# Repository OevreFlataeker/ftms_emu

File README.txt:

Used SDK 17.0.2
DevKit: NRF52DK

D:\nRF5_SDK_17.0.2_d674dde\examples\ble_central_and_peripheral\experimental\ble_app_cps_relay

Most of the headers comments have been explicitly removed in order to avoid confusion which parts are
genuine Nordic and which not

All 3rd party contrib stuff has been removed (FIT files, PCAP, BLE Sniffer, ...)

All Spec PDFs have been removed

---
---
---

Merged back to master

Do not forget to add the services 0x1814 (RCS) or 0x1816 (CSC) to the ADV Data! 
Otherwise it won't be found!

Macros
#define 	PM_CONN_SEC_ERROR_PIN_OR_KEY_MISSING   (PM_CONN_SEC_ERROR_BASE + 0x06)
 	Encryption failed because the peripheral has lost the LTK for this bond. See also BLE_HCI_STATUS_CODE_PIN_OR_KEY_MISSING and Table 3.7 ("Pairing Failed Reason Codes") in the Bluetooth Core Specification 4.2, section 3.H.3.5.5 (Bluetooth Core Specification).
	
#define 	PM_CONN_SEC_ERROR_DISCONNECT   (PM_CONN_SEC_ERROR_BASE + 0x100)
 	Pairing or encryption did not finish before the link disconnected for an unrelated reason.

When bonding fails, press Button 2 + RESET to delete bonding data.

Specifications:
https://github.com/oesmith/gatt-xml/blob/master/org.bluetooth.characteristic.csc_measurement.xml
https://www.bluetooth.org/docman/handlers/downloaddoc.ashx?doc_id=261450

At the moment this whole project needs to be placed into

$SDKROOT\examples\ble_central_and_peripheral\experimental\ble_app_cps_relay
because of the relative include directory setup

e.g. D:\nRF5_SDK_17.0.2_d674dde\examples\ble_central_and_peripheral\experimental\ble_app_cps_relay

Bike physics: https://www.physik.uni-wuerzburg.de/fileadmin/11010700/_imported/fileadmin/11010700/Didaktik/Zulassungsarbeiten/HA_1622196_Bielmeier_Carsten.pdf?
Section 5.2.3 - Free rolling

Formular free roll: v(t)=45*exp(-0.04*t)

Power measurement series:

Level 1:
76,58
77,59
79,61
80,62

Level 2:
74,67
75,69
77,71
78,72
79,73
80,75

Level 3:
75,80
76,81
79,84
80,86

Level 4:
76,94
77,96
78,98
79,100
80,102

Level 5:
77,110
78,112
80,116
81,117

Level 6:
75,120
76,120
78,124
78,124
79,126
80,128

Level 7:
75,129
76,131
77,133
78,135
81,141

Level 8:
75,141
77,145
78,148
80,153

Level 9:
76,157
77,159
78,162
80,168
80,168
80,169
84,175

Level 10:
80,178

Level 11:

74,173
75,175
76,178
77,181
78,184
79,187
79,187
80,190
80,190
82,136
Watt = 190-(rpm-80)*3

Level 12:
76,188
77,191
78,194
80,200
84,211
Watt = 200-(rpm-80)*3

Level 13:
76,198
77,201
78,204
79,207
80,210
Watt = 210-(rpm-80)*3

Level 14:
77,210
78,213
79,216
79,217
80,220
84,230
85,233
Watt = 220-(rpm-80)*3

Level 15:
72,204
73,207
74,210
75.215
80,230
82,232
82,235
85,238
Watt = 230-(rpm-80)*3

Level 16:
71,211
72,215
76,229
77,232
78,236
78,236
79,239
80,243
Watt = 236-(rpm-78)*4

Level 17:
72,229
74,233
75,237
76,240
76,240
77,244
78,247
Watt = 240+(rpm-76)*4

Level 18:
72,236
73,240
75,248
75,248
76,251
77,255
78,259
Watt = 248+(rpm-75)*4

Level 19:
74,253
75,257
76,261
77,265
Watt = 258+(rpm-75)*4

Level 20:
70,244
71,248
73,256
74,260
Watt = 260+(rpm-74)*4

Polar:
https://www.polar.com/sites/default/files/static/science/white-papers/polar-smart-calories-white-paper.pdf

Energy Expediture:
https://www.researchgate.net/publication/7777759_Prediction_of_energy_expenditure_from_heart_rate_monitoring_during_submaximal_exercise
EE = gender x (-55.0969 + 0.6309 x heart rate + 0.1988 x weight + 0.2017 x age)
+ (1 - gender) x (-20.4022 + 0.4472 x heartrate - 0.1263 x weight + 0.074 x age)
where gender = 1 for males and 0 for females. 

or:
https://www.sciencedirect.com/science/article/pii/S2095254612000464
for men, REE = 66.5 + 13.75 × weight (kg) + 5.003 × height (cm) − 6.775 × age; for women, REE = 655.1 + 9.563 × weight (kg) + 1.850 × height (cm) − 4.676 × age.

Calculator cadence:
https://www.omnicalculator.com/sports/bike-cadence-and-speed-calculator

https://www.bikecalc.com/speed_at_cadence

External buttons connection:

Candidates P0.11, P0.12, P0.22 + GND 

FTMS:
https://stackoverflow.com/questions/59653425/zwift-add-resistance-with-ftms-control-point

When an app like Zwift write to the CP it's an OP Code optionally followed by parameters, you should reply with the OP Code 0x80 (Response Code) followed by the OP Code that the reply is for, optionally followed by parameters.

In the case of OP Code 0x00 (Request Control) you should therefore reply with: 0x80, 0x00, 0x01. The last 0x01 is the result code for "Success".

In the case of OP Code 0x07 (Start/Resume), you should reply with: 0x80, 0x07, 0x01. Assuming you consider the request successful, the other possible responses are detailed in Table 4.24 of the FTMS Specification PDF.

On command you should look into is OP Code 0x11. When running Zwift in "non-workout mode", so just the normal mode, Zwift will use OP Code 0x11 followed by a set of simulation parameters: Wind Speed, Grade, Rolling resistance coeff and Wind resistance coeff. See the "4.16.2.18 Set Indoor Bike Simulation Parameters Procedure" of the PDF for details on the format of those parameters.

https://github.com/erikboto/ftms-example
https://forums.garmin.com/developer/connect-iq/f/app-ideas/206704/developing-a-ciq-ble-client-for-treadmill-and-fitness-equipment
Fitness Machine Service UUID: 0x1826
Fitness Machine Feature Characteristic 0x2acc 

Treadmill Data Characteristic 0x2acd
2902 Enable Notify Descriptor 0x2902
This is required so client gets more than one data point.
Supported Speed Range Characteristic 0x2ad4
Supported Incline Range Characteristic 0x2ad5
Keep Alive UUID

https://github.com/chadj/gpedal
https://devzone.nordicsemi.com/f/nordic-q-a/56370/bluetooth-ble-52832-try-to-implement-ftms-control-point-with-zwift
https://devzone.nordicsemi.com/f/nordic-q-a/56157/ble--nrfconnect-ftms-profile-indoor-bike-data-characteristic
https://devzone.nordicsemi.com/f/nordic-q-a/31046/how-to-support-ble-ftmp-profile
https://github.com/zacharyedwardbull/pycycling
The SufferFest, TrainerRoad, and Kinomap are the only two that I know of. 

ANT FE-C:
https://devzone.nordicsemi.com/f/nordic-q-a/44110/fe-c-support
https://github.com/vincent290587/ant_profiles

https://github.com/microsoft/BluetoothLEExplorer

https://stackoverflow.com/questions/64002583/decode-bluetooth-data-from-the-indoor-bike-data-characteristic/64004591#64004591

Tacx I/O FE-C
https://github.com/abellono/tacx-ios-bluetooth-example

https://github.com/jedla22/BleTrainerControl/blob/97f8fcefe4eb8563b768818658a1b480e10bd1b2/BleTrainerControl/BTLETrainerManager.m#L824
https://github.com/weinzmi/daumUSB2BLE/blob/master/BLE/fitness-control-point-characteristic.js#L128

Firmware download URL
https://device.tacxtraining.com/firmware/update.json

https://github.com/DigitalSecurity/nrf5x-tools

https://device.tacxtraining.com/firmware/neo_sb_pack_v0.0.40.zip

//Tacx FE-C service and characteristics
#define TACX_FEC_PRIMARY_SERVICE @"6E40FEC1-B5A3-F393-E0A9-E50E24DCCA9E"
//Pour détecter le Vortex
#define TACX_VORTEX_PRIMARY_SERVICE @"669AA305-0C08-969E-E211-86AD5062675F"

#define TACX_FEC_READ_CHARACTERISTIC @"6E40FEC2-B5A3-F393-E0A9-E50E24DCCA9E"
#define TACX_FEC_WRITE_CHARACTERISTIC @"6E40FEC3-B5A3-F393-E0A9-E50E24DCCA9E"

test: a4 09 4e 05 31 ff ff ff ff ff 90 01 b9 - set watt to 100W (= 400 * 0.25W)
test: a4 09 4e 05 31 ff ff ff ff ff 80 04 ac - set watt to 300w ( = 1200 * 0.25W)
test: a4 09 4e 05 33 ff ff ff ff 32 00 32 77 -  set incline to 50, roll resistance 0x32
test: a4 09 4e 05 33 ff ff ff ff 96 00 32 d3 -  set incline to 150
      a4 03 4e 05 46 47 ed - request data page 76 (last command)
	  a4 03 4e 05 46 10 ba - request type. 2nd byte in response = type of equipment (25 / 0x19 = Indoor bike)
Sync: 0xa4
Length: 0x09  (Data+Chk)
Type: 0x4e
Channel: 0x05
Data: 0x10 0x19 0x04 0x00 0x00 0x00 0xff 0x24
Chk(XOR of EVERYTHING): 0x30

Basline resistance values:
https://zwiftinsider.com/wahoo-kickr-tests-connecting-via-legacy-ant-ant-fe-c-and-bluetooth-ftms/
https://forums.zwift.com/t/baseline-resistance-too-low-in-sim-mode/497294

Trainer force curves:
http://www.powercurvesensor.com/cycling-trainer-power-curves/

https://devzone.nordicsemi.com/f/nordic-q-a/23316/nrf_error_no_mem

https://bicycles.stackexchange.com/questions/49732/does-changing-gear-relation-produce-different-speed-at-same-applied-power

Power via battery:

USB and coin cell at the same time is OK as long as protection diodes are not shorted: https://devzone.nordicsemi.com/f/nordic-q-a/44780/can-we-supply-power-from-both-usb-and-coin-cell-battery

Infos about battery:
https://www.dmcinfo.com/Portals/0/Blog%20Files/High%20pulse%20drain%20impact%20on%20CR2032%20coin%20cell%20battery%20capacity.pdf

Info about nrf51 sampling battery voltage via saadc
https://github.com/NordicPlayground/nrf51-ADC-examples/blob/master/ble_app_hrs_adc_battery_measurement/main.c

There should be an Input PIN 
https://github.com/NordicPlayground/nRF52-ADC-examples
https://github.com/NordicPlayground/nRF52-ADC-examples/blob/master/ble_app_uart__saadc_timer_driven__scan_mode/main.c

nrf_saadc_input_t NRF_SAADC_INPUT_VDD
nrf_saadc_reference_t NRF_SAADC_REFERENCE_VDD4 
battery_level_in_percent in https://infocenter.nordicsemi.com/topic/sdk_nrf5_v17.0.2/group__app__util.html

Important finding: The DK52 has protection diodes on all 3 powering options which lead to a drop of 0.5V on every option. Instead of 3.3V via USB its only 2.8V, Instead of 3V for the coin cell, its only 2.5V... My calculations for the triggering of the home trainer are based on a voltage of 3V (resistor, current, ..). The voltage of 2.5V is too low to trigger the shift! Actually, even at 2.8V it's a wonder it actually works...

USB A Host Interface: https://learn.sparkfun.com/tutorials/usb-type-a-female-breakout-hookup-guide/all

Central micro on hometrainer is presumably a Reneasas R8C/24, https://www.digchip.com/datasheets/parts/datasheet/192/R5F21258SNFP-pdf.php
Latest datasheet https://www.renesas.com/br/en/document/dst/r8c24-r8c25-group-datasheet?language=en&r=1053566

Hometrainer, 4 pin "Sensor" Cable:
(Note: Colors are relativ to my Y-Splitter cable!)
Yellow: GND
Red: Power settings, ranging from 1.375V (Resistance 1) to 3.9V (Resistance 32) [1: 1.375V, 10: 2.4V, 20: 3.18V, 30: 3.8V, 32: 3.9V]
White: 5V, Cadence signal, on every full revolution, signal goes Low for n ms (100?)
Black: 12V, can be used to get some voltage

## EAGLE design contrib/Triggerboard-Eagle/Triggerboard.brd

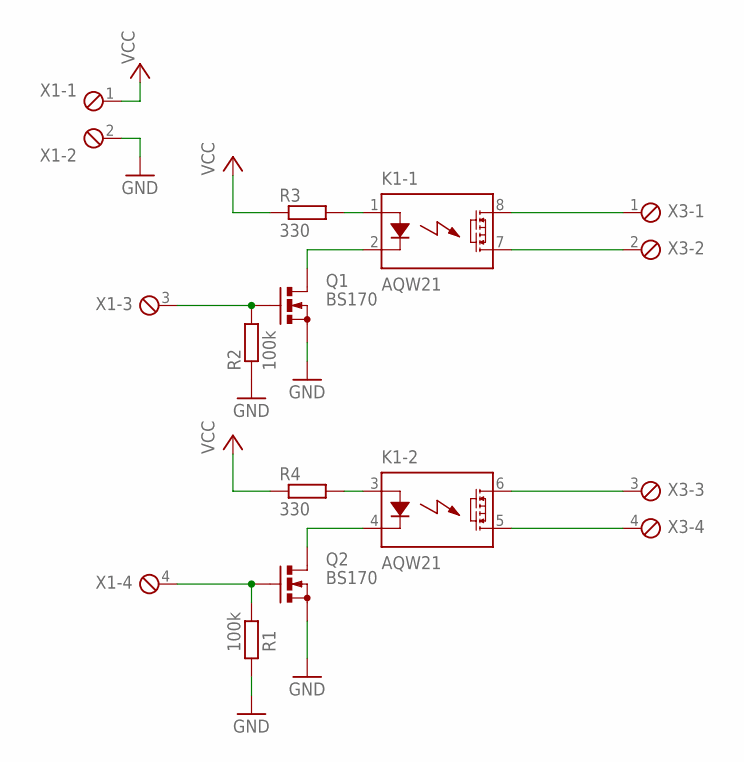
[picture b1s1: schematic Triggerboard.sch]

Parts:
K1: AQW21; DIL08; MPN AQW210EH
Q1, Q2: BS170; SOT54E; MPN BS170
R1, R2: 100k; 0207/12
R3, R4: 330; 0207/12; MPN MCF 1W 330R
X1, X3: MPT4; 4POL254

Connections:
GND: Q1.S, Q2.S, R1.2, R2.1, X1.2
unnamed: K1.1 (A), R3.2
unnamed: K1.3 (A), R4.2
unnamed: Q2.G, R1.1, X1.4
unnamed: K1.8 (D1), X3.1
unnamed: K1.4 (K), Q2.D
unnamed: K1.5 (D2), X3.4
unnamed: K1.6 (D1), X3.3
unnamed: K1.7 (D2), X3.2
unnamed: K1.2 (K), Q1.D
unnamed: Q1.G, R2.2, X1.3
VCC: R3.1, R4.1, X1.1

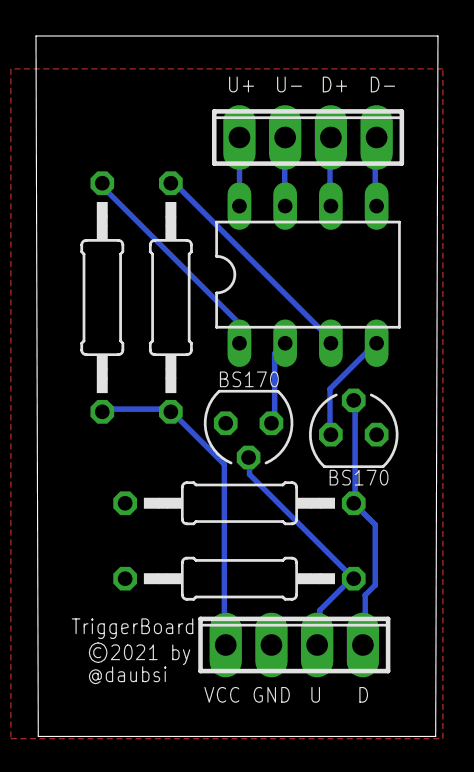
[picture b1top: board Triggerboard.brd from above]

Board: 2 copper layers, 22.3 x 38.9 mm, 9 parts (0 on the bottom side), 12 nets.

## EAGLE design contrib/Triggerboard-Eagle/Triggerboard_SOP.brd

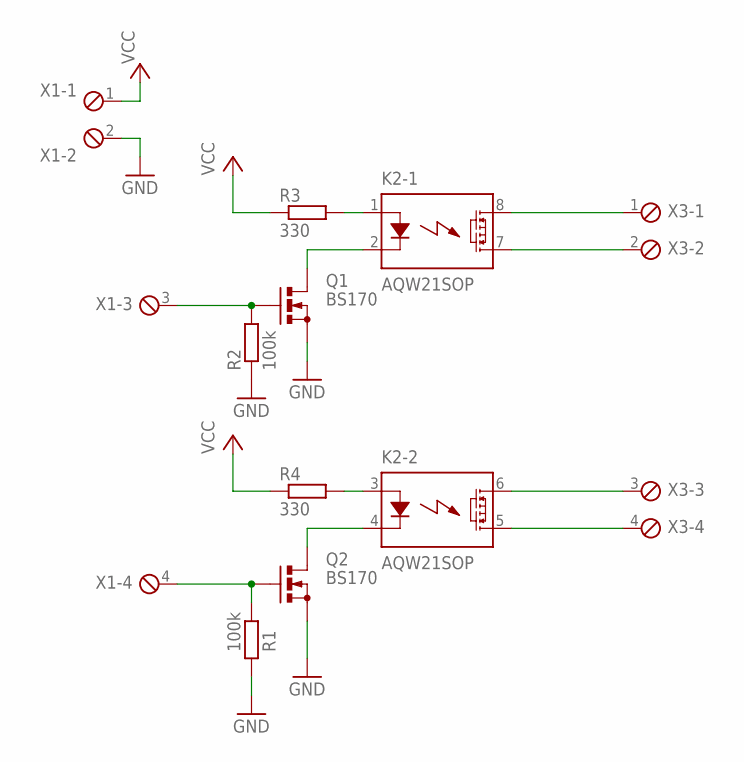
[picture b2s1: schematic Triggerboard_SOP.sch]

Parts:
K2: AQW21SOP; SOP08
Q1, Q2: BS170; SOT54E; MPN BS170
R1, R2: 100k; 0207/12
R3, R4: 330; 0207/12; MPN MCF 1W 330R
X1, X3: MPT4; 4POL254

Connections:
GND: Q1.S, Q2.S, R1.2, R2.1, X1.2
unnamed: K2.1 (A), R3.2
unnamed: K2.3 (A), R4.2
unnamed: Q2.G, R1.1, X1.4
unnamed: K2.8 (D1), X3.1
unnamed: K2.4 (K), Q2.D
unnamed: K2.5 (D2), X3.4
unnamed: K2.6 (D1), X3.3
unnamed: K2.7 (D2), X3.2
unnamed: K2.2 (K), Q1.D
unnamed: Q1.G, R2.2, X1.3
VCC: R3.1, R4.1, X1.1

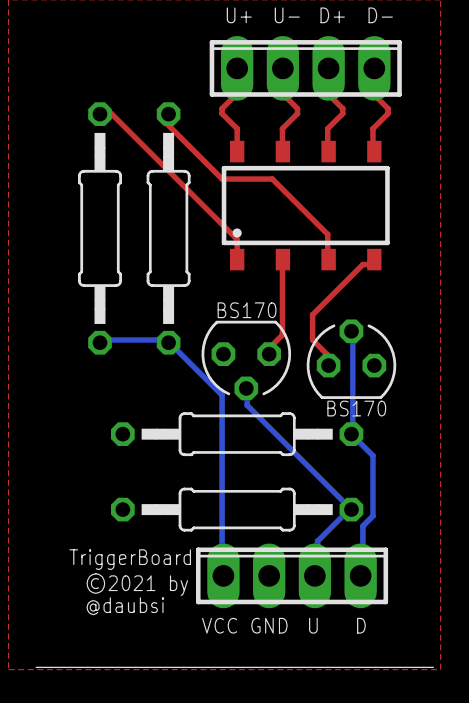
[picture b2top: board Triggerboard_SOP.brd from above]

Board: 2 copper layers, 9 parts (0 on the bottom side), 12 nets.

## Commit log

2022-12-27 Initial commit of sources

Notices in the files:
contrib/Triggerboard-Eagle/Triggerboard.brd:
©2021 by
@daubsi
